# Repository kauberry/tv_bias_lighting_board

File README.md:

## Controller for Television Bias Lighting with LED strips ##

### Background ###
I wanted to have a bias lighting system for my wall mounted TV's such that the lights would be controlled by the TV itself through one of its built-in USB ports, but still be actually powered from a 12v power adapter, so as not to overrun the USB port's current ratings.

The whole show is being run by an ATTiny85 AVR chip that is listening to the USB port on the TV (through an optocoupler), waiting for the set to power up/down, and fading the lights up or down as appropriate.

### Availability ###
I've made the project available on OSHPark, for anyone who is interested. The version up right now is currently untested in physical form, so order at your own risk. Once I get my boards back, I'll update.

https://oshpark.com/shared_projects/4CxVxJLe

#### Bill of Materials
Quantity | Item                         | Part Number / Identifier
:--------: | -------------------------- | -------------------
  1    | ATTiny85 8-pin SOIC AVR Chip | ATTiny85
  1    | 5.5mm Power Jack             | DCJ0202
  1    | MicroUSB SMD Jack            | *
  1    | 2 Position Terminal Block    | *
  3    | 10kΩ 1206 Chip Resistor      | *
  1    | 1kΩ 1206 Chip Resistor       | *
  1    | 150Ω 1206 Chip Resistor      | *
  1    | 0.1µF 1206 Chip Capacitor    | *
  1    | SMA-form factor Schottky Diode | *
  1    | Single-channel Optocoupler   | Sharp EL817
  1    | LDO 5V Regulator (SOT-223)   | *
  1    | N-channel MosFET Transistor  | IRLML2502

#### Prototype Board Images
These are the pre-production renders of the board proper, straight from [OSH Park](http://oshpark.com)

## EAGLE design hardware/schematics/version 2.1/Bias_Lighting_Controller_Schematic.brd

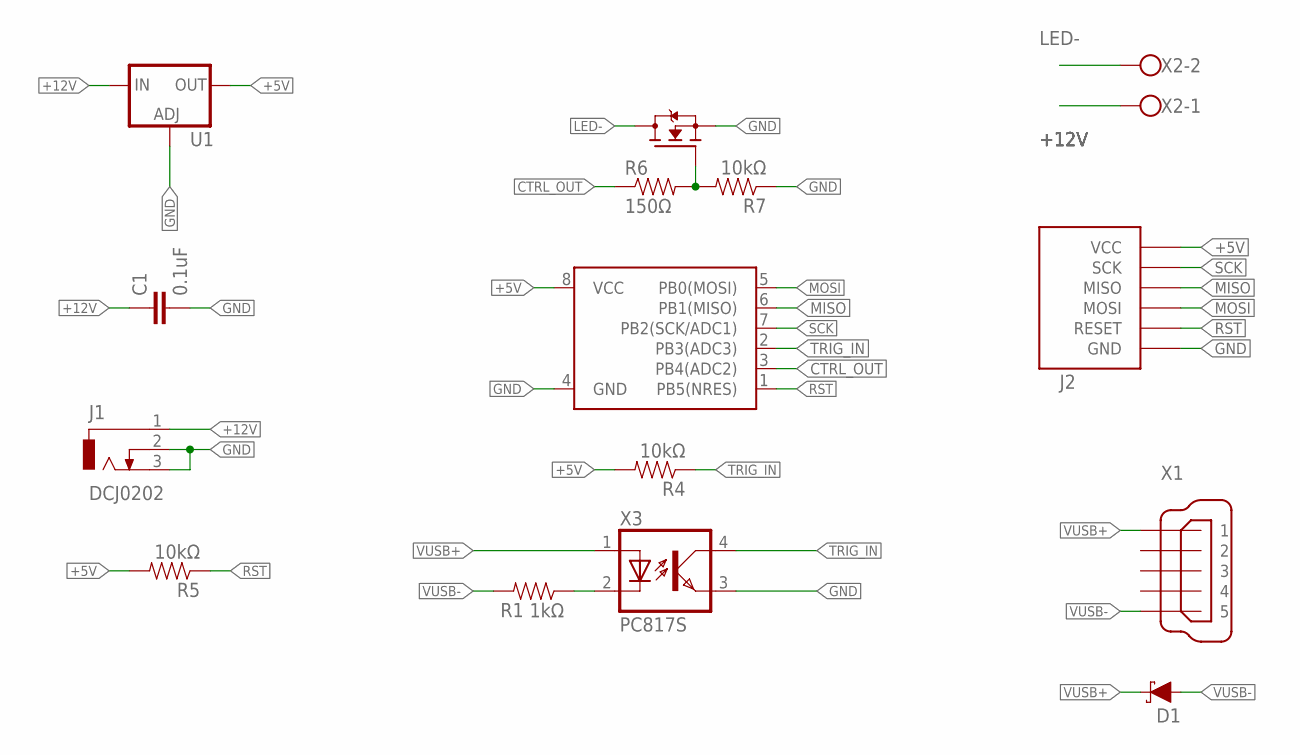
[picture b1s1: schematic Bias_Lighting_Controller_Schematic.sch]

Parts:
ATTINY85: ATTINY45; SO08-EIAJ
C1: 0.1uF; C1206K
D1: DIODE-SCHOTTKY-SS14; SMA-DIODE
IRF740_MOSFET1: MOSFET-N-SOT23; SOT23
J1: DCJ0202
J2: AVR_MICRO_ICP
R1: 1kΩ; 1206
R4, R5, R7: 10kΩ; 1206
R6: 150Ω; 1206
U1: V_REG_317SMD; SOT223
X1: MINI-USB-UX60-MB-5ST; UX60-MB-5ST
X2: W237-102
X3: PC817S; PC817SMT

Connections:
+5V: ATTINY85.8 (VCC), J2.VCC, R4.2, R5.2, U1.2 (OUT)
+12V: C1.1, J1.1, U1.3 (IN), X2.1
CTRL_OUT: ATTINY85.3 (PB4(ADC2)), R6.1
GND: ATTINY85.4 (GND), C1.2, IRF740_MOSFET1.2 (S), J1.2, J1.3, J2.GND, R7.1, U1.1 (ADJ), X3.3 (EMIT)
LED-: IRF740_MOSFET1.3 (D), X2.2
MISO: ATTINY85.6 (PB1(MISO)), J2.MISO
MOSI: ATTINY85.5 (PB0(MOSI)), J2.MOSI
unnamed: IRF740_MOSFET1.1 (G), R6.2, R7.2
RST: ATTINY85.1 (PB5(NRES)), J2.RESET, R5.1
SCK: ATTINY85.7 (PB2(SCK/ADC1)), J2.SCK
TRIG-: R1.1, X3.2 (C)
TRIG_IN: ATTINY85.2 (PB3(ADC3)), R4.1, X3.4 (COL)
VUSB+: D1.C, X1.1, X3.1 (A)
VUSB-: D1.A, R1.2, X1.5

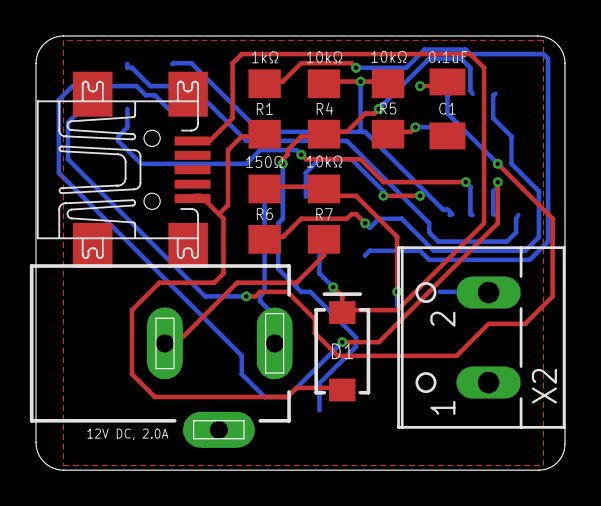
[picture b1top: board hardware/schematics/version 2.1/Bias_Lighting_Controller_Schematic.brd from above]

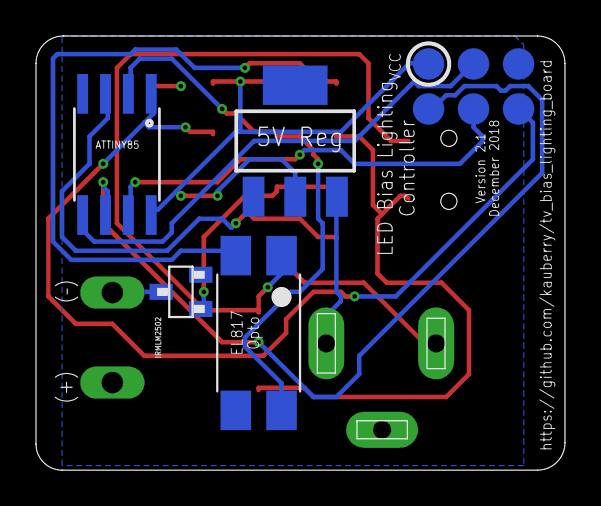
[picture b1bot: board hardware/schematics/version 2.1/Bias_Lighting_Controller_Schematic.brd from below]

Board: 2 copper layers, 29.4 x 24.1 mm, 15 parts (5 on the bottom side), 14 nets.

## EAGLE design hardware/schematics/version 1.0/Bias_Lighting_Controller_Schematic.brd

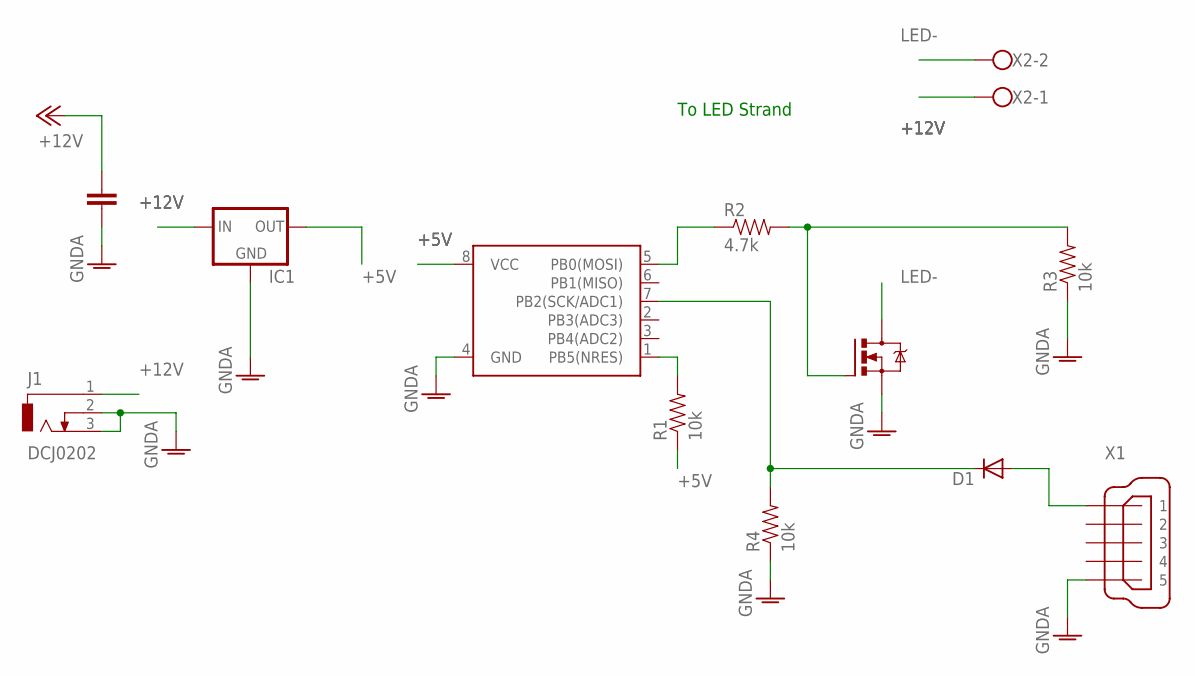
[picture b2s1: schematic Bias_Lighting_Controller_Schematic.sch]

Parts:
C1: CAP1206; 1206
D1: DIODESMA; SMA-DIODE
IC1: 78LXX
IRF740_MOSFET: IRF740; TO220BV
J1: DCJ0202
R1, R3, R4: 10k; 1206
R2: 4.7k; 1206
U$1: ATTINY45DIP8; DIP08
X1: MINI-USB-UX60-MB-5ST; UX60-MB-5ST
X2: W237-102

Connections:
+5V: IC1.OUT, R1.1, U$1.8 (VCC)
+12V: C1.2, IC1.IN, J1.1, X2.1
GNDA: C1.1, IC1.GND, IRF740_MOSFET.S, J1.2, J1.3, R3.1, R4.1, U$1.4 (GND), X1.5
LED-: IRF740_MOSFET.D, X2.2
unnamed: R1.2, U$1.1 (PB5(NRES))
unnamed: R2.1, U$1.5 (PB0(MOSI))
unnamed: D1.A, X1.1
unnamed: IRF740_MOSFET.G, R2.2, R3.2
unnamed: D1.C, R4.2, U$1.7 (PB2(SCK/ADC1))

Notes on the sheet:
To LED Strand

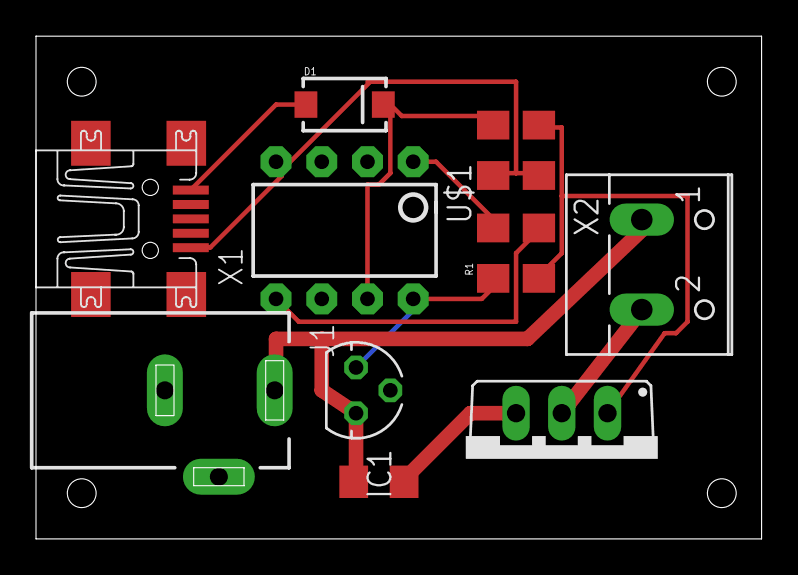
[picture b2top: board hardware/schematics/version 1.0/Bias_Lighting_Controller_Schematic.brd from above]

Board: 2 copper layers, 40.3 x 27.9 mm, 12 parts (0 on the bottom side), 9 nets.

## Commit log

2018-03-17 Committing initial firmware code
2018-11-28 Updated the board design to use more SMD components
2018-11-28 Adding documentation and labeled board files
2018-12-14 Adding AVR-ISP pads to existing board for easier programming

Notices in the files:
parts and their libraries:
SparkFun-DigitalIC: Licensing: CC v3.0 Share-Alike You are welcome to use this library for commercial purposes.
SparkFun-IC-Power: Licensing: Creative Commons ShareAlike 4.0 International - https://creativecommons.org/licenses/by-sa/4.0
